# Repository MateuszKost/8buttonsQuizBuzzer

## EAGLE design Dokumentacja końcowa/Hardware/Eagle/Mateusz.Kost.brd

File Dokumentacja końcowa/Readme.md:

Mateusz Kost grupa 4, inf semestr 5

Projekt o nazwie „8 kanałowy dzwonek do quizu” posiadał poniższe założenia:
- informacja wciśniętym guziku (jego numer) będzie adekwatnie wyświetlana na wyświetlaczu
- w przypadku wciśnięcia dwóch guzików, minimalna różnica czasowa przy ich wciskaniu zostanie wychwycona przez program oraz informacja o szybciej wciśniętym guziku zostanie pokazana na wyświetlaczu
- po wychwyceniu wciśnięcia guzika, program wyśle sygnał do buzzera, który zadzwoni

Wersja finalna projektu spełnia wszystkie powyższe założenia, a do samego projektu dołożyłem jeszcze 3 diody sygnalizujące o adekwatnym stanie programu.

Funkcjonalność urządzenia opiera się na wciskaniu jednego z 8 guzików sterujących, a po wyświetleniu informacji na wyświetlaczu na temat wciśniętego guzika należy wcisnąć guzik reset, który wysyła informacje do programu aby zresetował wyświetlacz i pozwolił na ponowną możliwość wciśnięcia guzika sterującego.

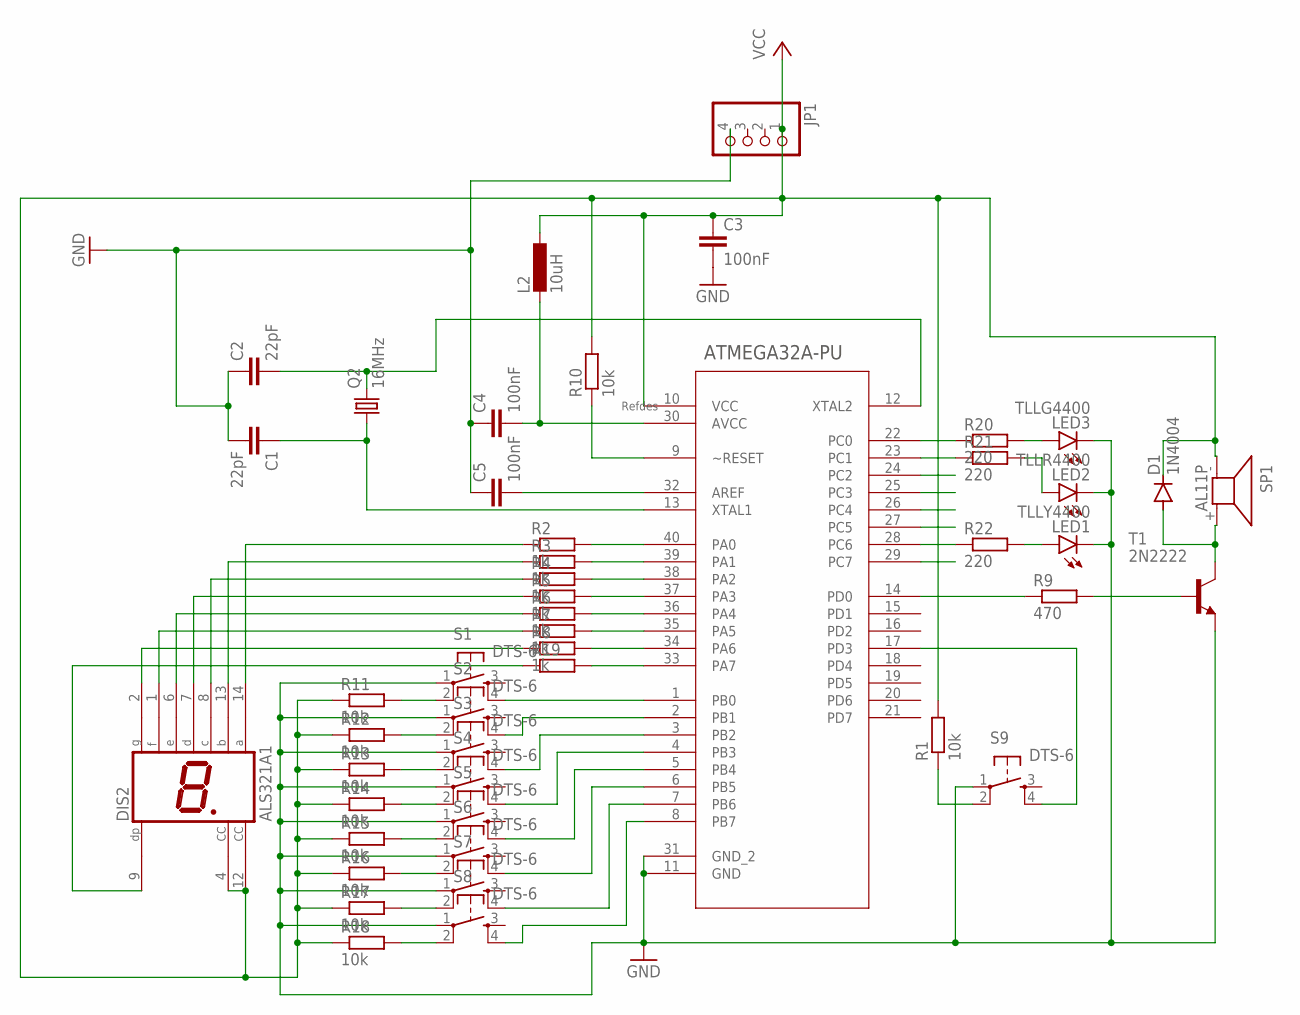
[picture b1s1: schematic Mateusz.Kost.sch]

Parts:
C1, C2: 22pF; C2.5-2
C3, C4, C5: 100nF; C2.5-2
D1: 1N4004; DO41-10
DIS2: ALS321A1
JP1: PINHD-1X4; 1X04
L2: 10uH; 0204/5
LED1: TLLY4400; LED3MM
LED2: TLLR4400; LED3MM
LED3: TLLG4400; LED3MM
Q2: 16MHz; HC49/S
R1, R10, R11, R12, R13, R14, R15, R16, R17, R18: 10k; 0204/7
R2, R3, R4, R5, R6, R7, R8, R19: 1k; 0204/7
R9: 470; 0204/7
R20, R21, R22: 220; 0204/7
S1, S2, S3, S4, S5, S6, S7, S8, S9: DTS-6
SP1: AL11P
T1: 2N2222; TO18
U1: ATMEGA32A-PU; DIP254P1524X482-40

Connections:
GND: C1.2, C2.1, C3.2, C4.1, C5.1, JP1.4, LED1.K (C), LED2.K (C), LED3.K (C), S1.1, S2.1, S3.1, S4.1, S5.1, S6.1, S7.1, S8.1, S9.1, T1.1 (E), U1.11 (GND), U1.31 (GND_2)
unnamed: R9.1, U1.14 (PD0)
unnamed: R1.1, S9.2
unnamed: R11.2, S1.2
unnamed: S1.4, U1.1 (PB0)
unnamed: S2.4, U1.2 (PB1)
unnamed: S3.4, U1.3 (PB2)
unnamed: S4.4, U1.4 (PB3)
unnamed: S5.4, U1.5 (PB4)
unnamed: S6.4, U1.6 (PB5)
unnamed: R20.1, U1.22 (PC0)
unnamed: LED2.A, R21.2
unnamed: LED1.A, R22.2
unnamed: S7.4, U1.7 (PB6)
unnamed: R12.2, S2.2
unnamed: R13.2, S3.2
unnamed: R14.2, S4.2
unnamed: R15.2, S5.2
unnamed: R16.2, S6.2
unnamed: R17.2, S7.2
unnamed: R18.2, S8.2
unnamed: C2.2, Q2.2, U1.12 (XTAL2)
unnamed: R9.2, T1.2 (B)
unnamed: S9.4, U1.17 (PD3)
unnamed: D1.A, SP1.+ (2), T1.3 (C)
unnamed: C4.2, L2.2, U1.30 (AVCC)
unnamed: C5.2, U1.32 (AREF)
unnamed: R10.1, U1.9 (~RESET)
unnamed: C1.1, Q2.1, U1.13 (XTAL1)
unnamed: R2.2, U1.40 (PA0)
unnamed: R3.2, U1.39 (PA1)
unnamed: R4.2, U1.38 (PA2)
unnamed: R5.2, U1.37 (PA3)
unnamed: R6.2, U1.36 (PA4)
unnamed: R7.2, U1.35 (PA5)
unnamed: R8.2, U1.34 (PA6)
unnamed: R19.2, U1.33 (PA7)
unnamed: DIS2.14 (A), R2.1
unnamed: DIS2.13 (B), R3.1
unnamed: DIS2.8 (C), R4.1
unnamed: DIS2.7 (D), R5.1
unnamed: DIS2.6 (E), R6.1
unnamed: DIS2.1 (F), R7.1
unnamed: DIS2.2 (G), R8.1
unnamed: DIS2.9 (DP), R19.1
unnamed: LED3.A, R20.2
unnamed: R21.1, U1.23 (PC1)
unnamed: R22.1, U1.28 (PC6)
unnamed: S8.4, U1.8 (PB7)
VCC: C3.1, D1.C, DIS2.4 (CC), DIS2.12 (CC), JP1.1, L2.1, R1.2, R10.2, R11.1, R12.1, R13.1, R14.1, R15.1, R16.1, R17.1, R18.1, SP1.- (1), U1.10 (VCC)

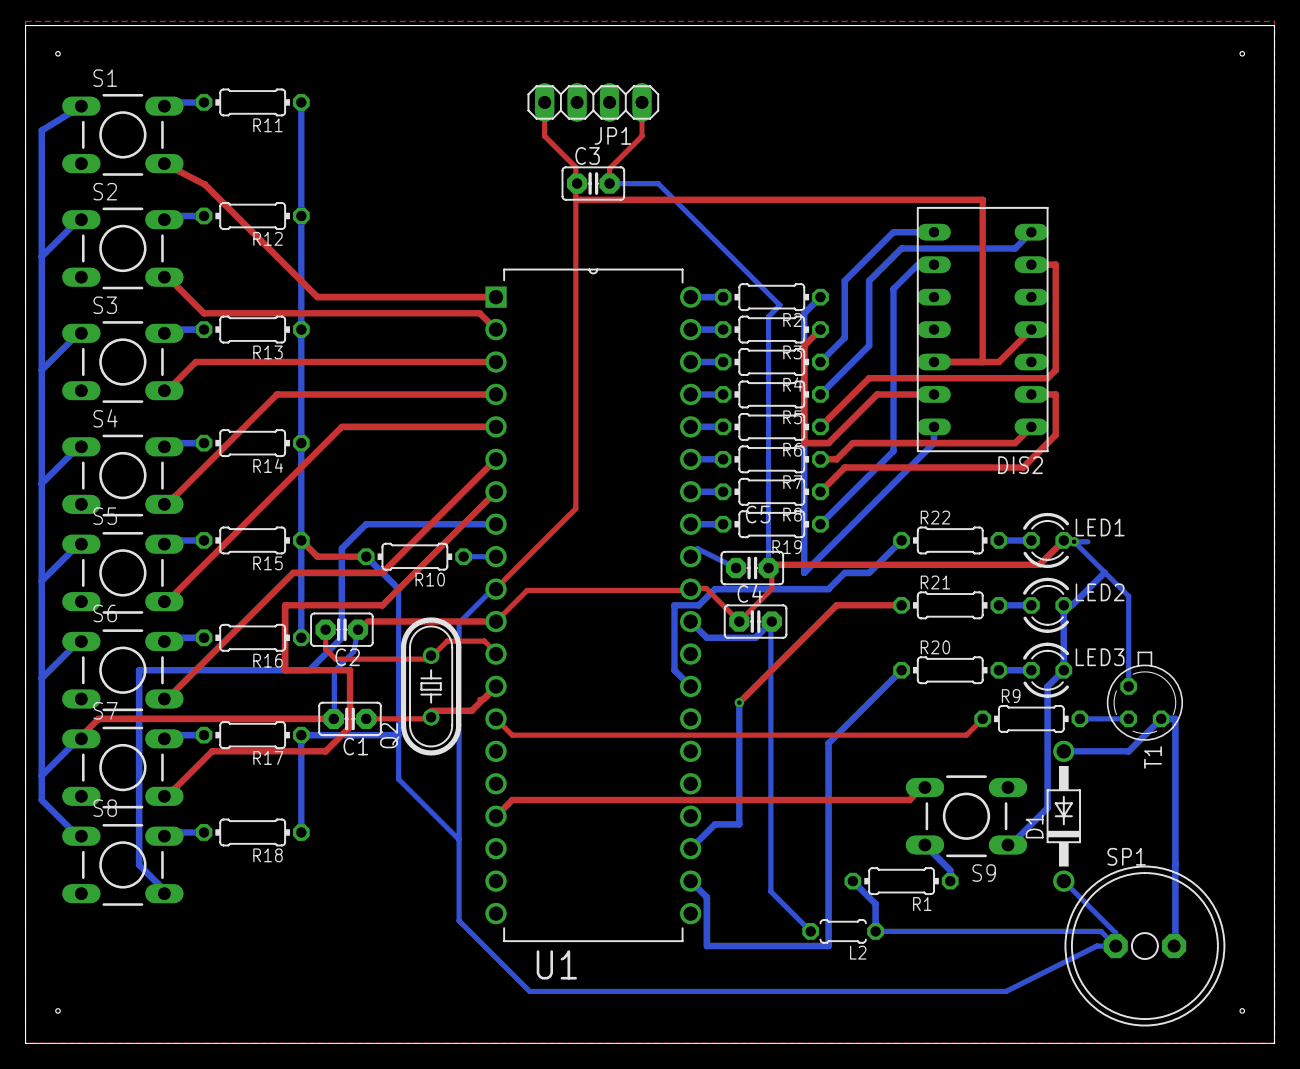
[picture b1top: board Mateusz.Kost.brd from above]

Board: 2 copper layers, 97.8 x 79.7 mm, 47 parts (0 on the bottom side), 50 nets.
